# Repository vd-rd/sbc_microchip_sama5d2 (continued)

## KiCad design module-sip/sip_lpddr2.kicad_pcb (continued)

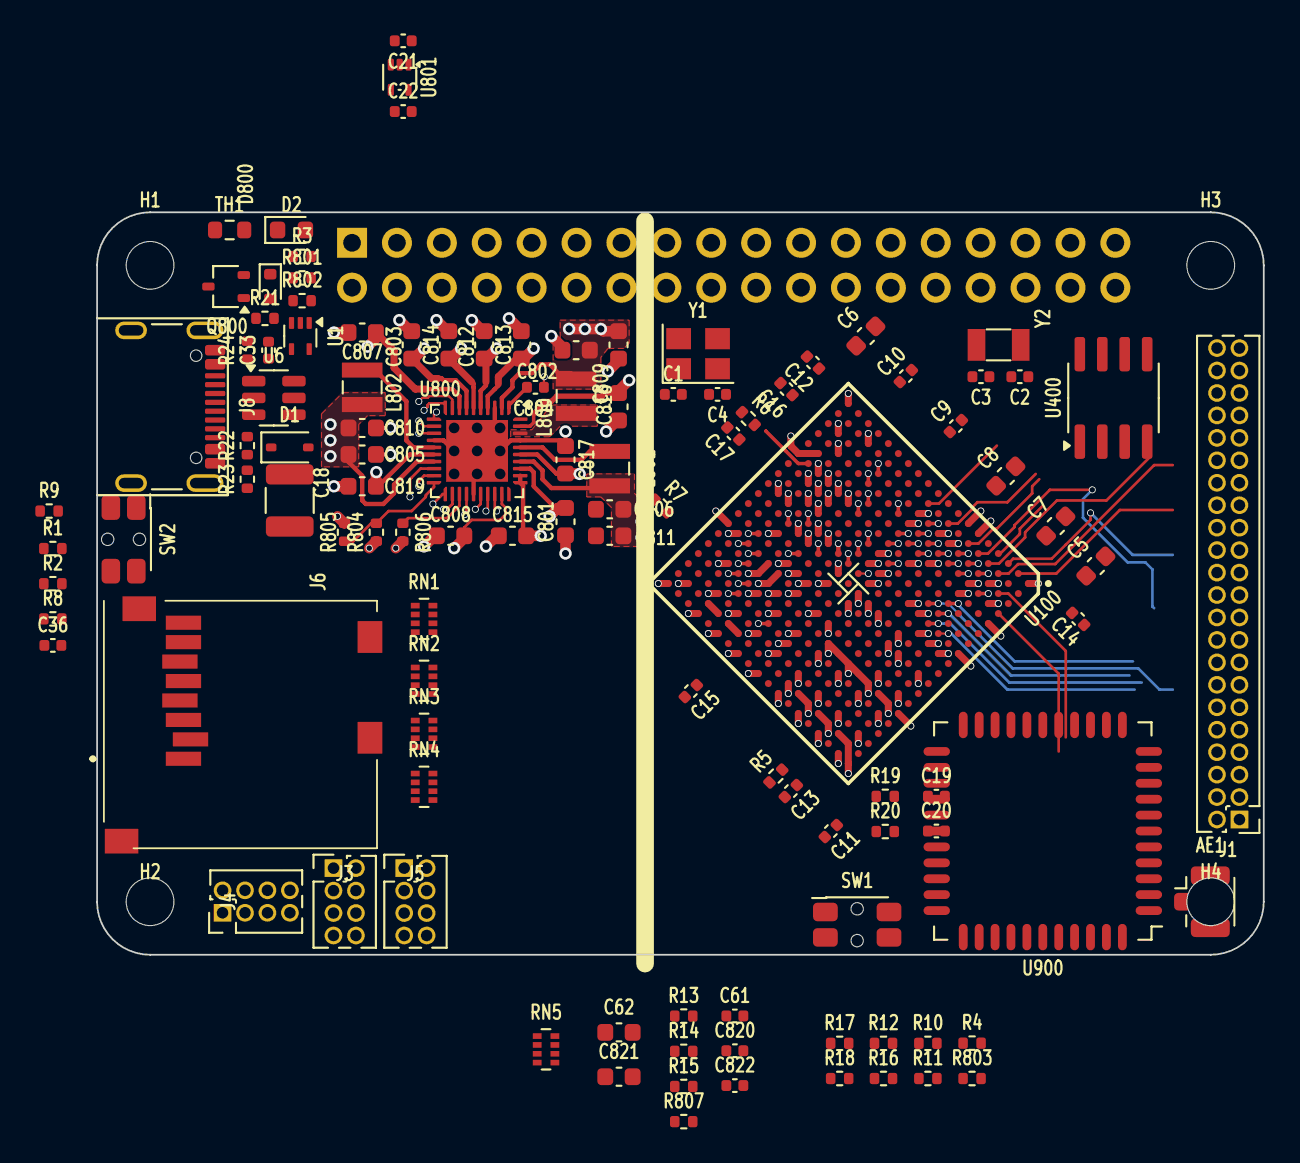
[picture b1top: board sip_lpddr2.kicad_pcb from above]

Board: 4 copper layers, 66.0 x 42.0 mm, 114 parts (1 on the bottom side), 124 nets.

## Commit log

2025-12-15 initial push
2025-12-15 add project files
2026-02-03 backport board changes
2026-02-04 optimized pmic layout
2026-02-05 added usbc connector
2026-02-06 backport from sam9x60
2026-05-02 updated gitignore and bump to kicad 10
2026-05-03 added flexcomm tables
